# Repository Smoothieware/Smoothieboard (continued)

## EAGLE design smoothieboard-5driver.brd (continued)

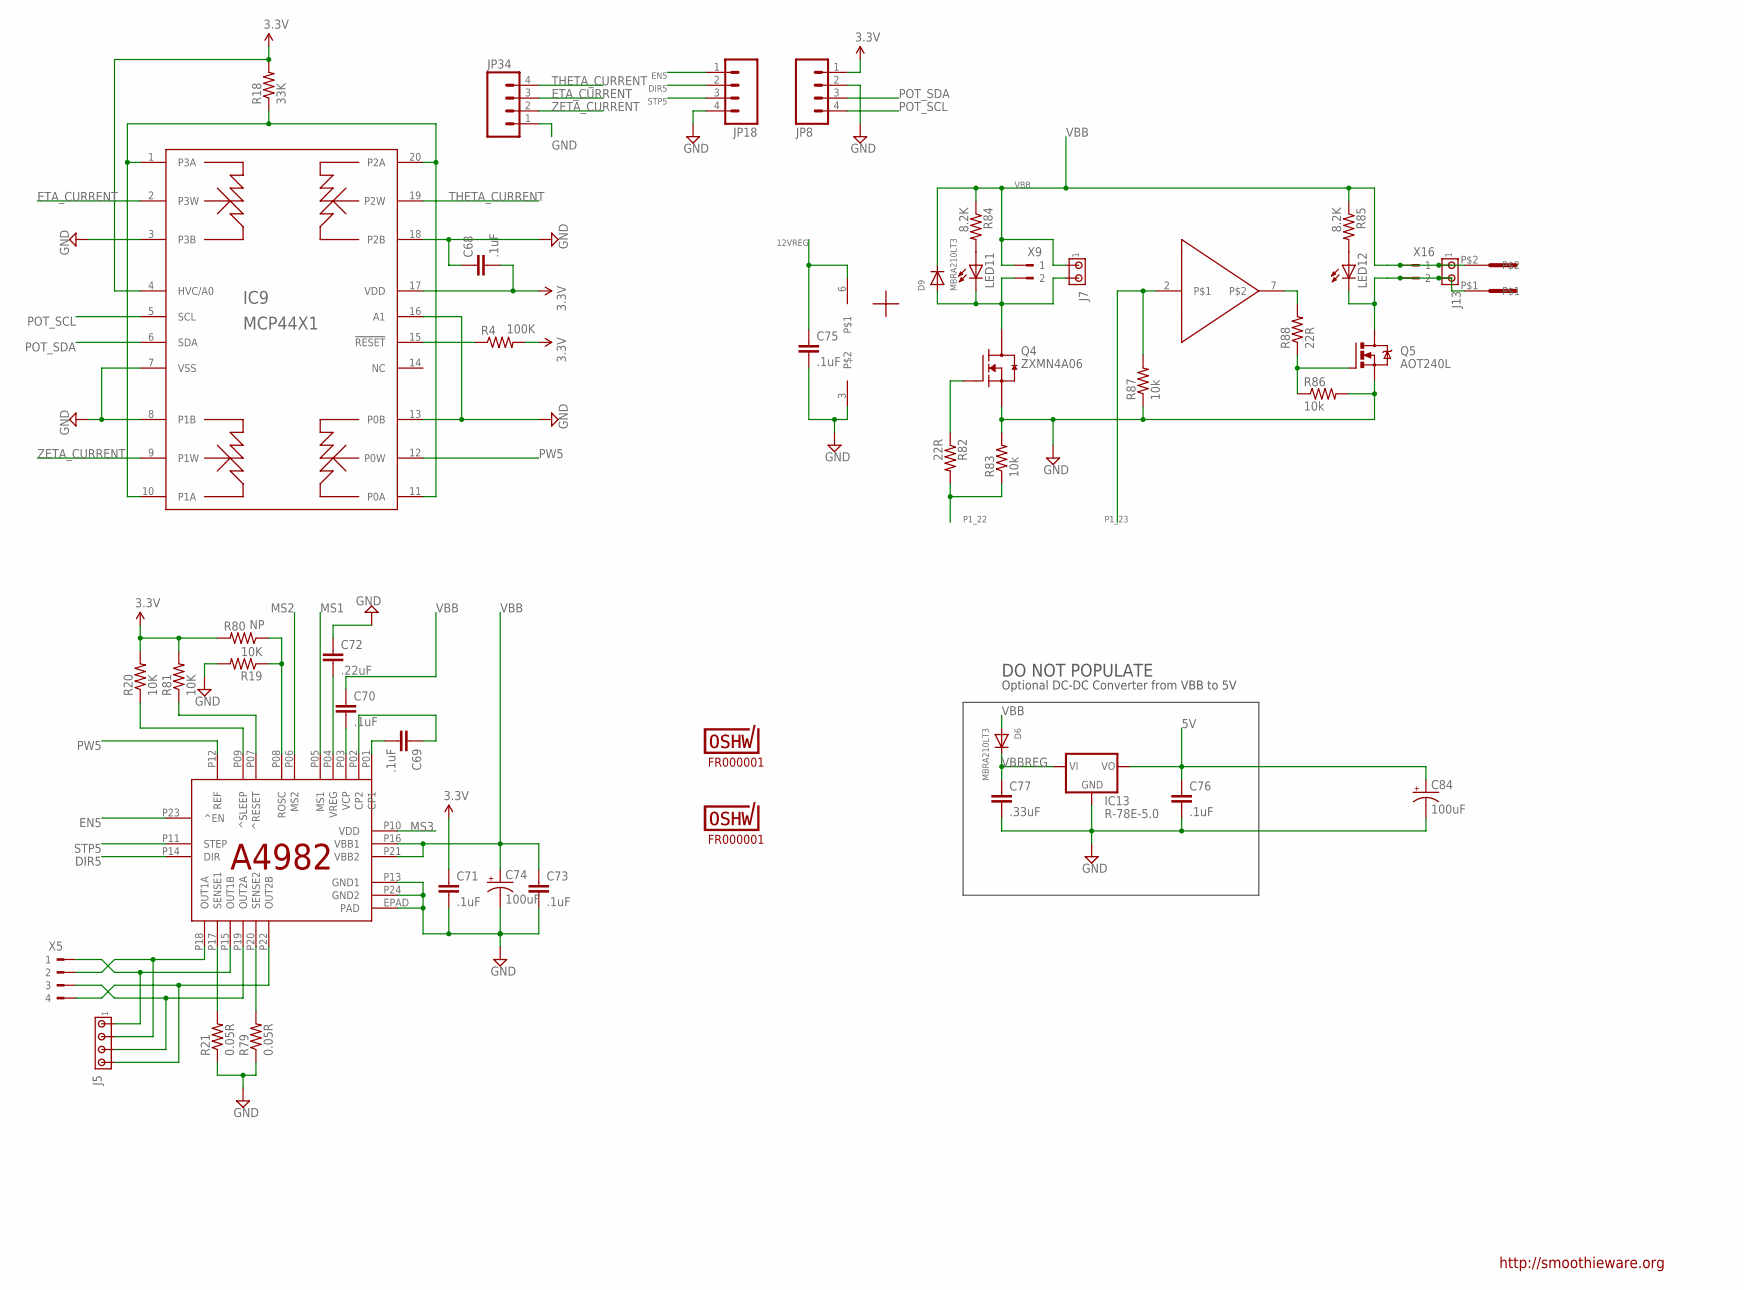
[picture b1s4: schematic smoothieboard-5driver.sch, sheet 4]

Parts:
C68, C69, C70, C71, C73, C75, C76: .1uF; C0603
C72: .22uF; C0603
C74: 100uF; PANASONIC_E
C77: .33uF; C0603
C84: 100uF; PANASONIC_D
D6, D9: MBRA210LT3; SMADIODE
IC9: MCP44X1; TSSOP20
IC12: A5984; ETSSOP24
IC13: R-78E-5.0; R-78
IC15: TC4427; SOIC8
J5: MTA04-100; 10X04MTA
J7, J13: MTA02-100; 10X02MTA
JP8, JP18, JP34: M041X04_NO_SILK; 1X04_NO_SILK
LED11, LED12: LEDCHIP-LED0805; CHIP-LED0805
Q4: ZXMN4A06; SOT230P700X160-4N
Q5: AOT240L; TO220BV
R4: 100K; R0603
R18: 33K; R0603
R19, R20, R81: 10K; R0603
R21, R79: 0.05R; R2512
R80: NP; R0603
R82, R88: 22R; R0603
R83, R86, R87: 10k; R0603
R84, R85: 8.2K; R0603
U$7: 5MMCONN; 1715250000
U$11: FR000001; CERT-SMALL-SILK
U$12: FR000001; CERT-MED-SILK
X5: 180G-4
X9, X16: 180G-2

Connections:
3.3V: C68.2, C71.1, IC9.4 (HVC/A0), IC9.17 (VDD), JP8.1, R4.2, R18.2, R20.2, R80.2, R81.2; also elsewhere on the board
5V: C76.1, C84.+, IC13.3 (VO); also elsewhere on the board
12VREG: C75.1, IC15.6; also elsewhere on the board
DIR5: IC12.P14 (DIR), JP18.2; also elsewhere on the board
EN5: IC12.P23 (^EN), JP18.1; also elsewhere on the board
ETA_CURRENT: IC9.2 (P3W), JP34.3
GND: C68.1, C71.2, C72.1, C73.2, C74.-, C75.2, C76.2, C77.2, C84.-, IC9.3 (P3B), IC9.7 (VSS), IC9.8 (P1B), IC9.13 (P0B), IC9.16 (A1), IC9.18 (P2B), IC12.EPAD (PAD), IC12.P13 (GND1), IC12.P24 (GND2), IC13.2 (GND), IC15.3, JP8.2, JP18.4, JP34.1, Q4.3 (S), Q5.S, R19.2, R21.1, R79.1, R83.2, R86.2, R87.1; also elsewhere on the board
GPIO_FET1: Q5.G, R86.1, R88.1
MS1: IC12.P05 (MS1); also elsewhere on the board
MS2: IC12.P06 (MS2); also elsewhere on the board
MS3: IC12.P10 (VDD); also elsewhere on the board
unnamed: IC9.15 (!RESET), R4.1
unnamed: D9.A, J7.2, LED11.C, Q4.4 (D), X9.2
unnamed: IC9.1 (P3A), IC9.10 (P1A), IC9.11 (P0A), IC9.20 (P2A), R18.1
unnamed: C69.2, IC12.P01 (CP1)
unnamed: C69.1, IC12.P02 (CP2)
unnamed: C70.2, IC12.P03 (VCP)
unnamed: IC12.P17 (SENSE1), R21.2
unnamed: IC12.P20 (SENSE2), R79.2
unnamed: IC12.P18 (OUT1A), J5.2, X5.2
unnamed: IC12.P15 (OUT1B), J5.1, X5.1
unnamed: IC12.P19 (OUT2A), J5.3, X5.3
unnamed: IC12.P22 (OUT2B), J5.4, X5.4
unnamed: IC12.P08 (ROSC), R19.1, R80.1
unnamed: C72.2, IC12.P04 (VREG)
unnamed: IC12.P09 (^SLEEP), R20.1
unnamed: IC12.P07 (^RESET), R81.1
unnamed: Q4.1 (G), R82.1
unnamed: LED11.A, R84.2
unnamed: J13.2, LED12.C, Q5.D, U$7.P$1, X16.2
unnamed: LED12.A, R85.2
unnamed: IC15.7, R88.2
P1_22: R82.2, R83.1; also elsewhere on the board
P1_23: IC15.2, R87.2; also elsewhere on the board
POT_SCL: IC9.5 (SCL), JP8.4; also elsewhere on the board
POT_SDA: IC9.6 (SDA), JP8.3; also elsewhere on the board
PW5: IC9.12 (P0W), IC12.P12 (REF)
STP5: IC12.P11 (STEP), JP18.3; also elsewhere on the board
THETA_CURRENT: IC9.19 (P2W), JP34.4
VBB: C70.1, C73.1, C74.+, D6.A, D9.C, IC12.P16 (VBB1), IC12.P21 (VBB2), J7.1, J13.1, R84.1, R85.1, U$7.P$2, X9.1, X16.1; also elsewhere on the board
VBBREG: C77.1, D6.C, IC13.1 (VI)
ZETA_CURRENT: IC9.9 (P1W), JP34.2

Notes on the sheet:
http://smoothieware.org
DO NOT POPULATE
Optional DC-DC Converter from VBB to 5V

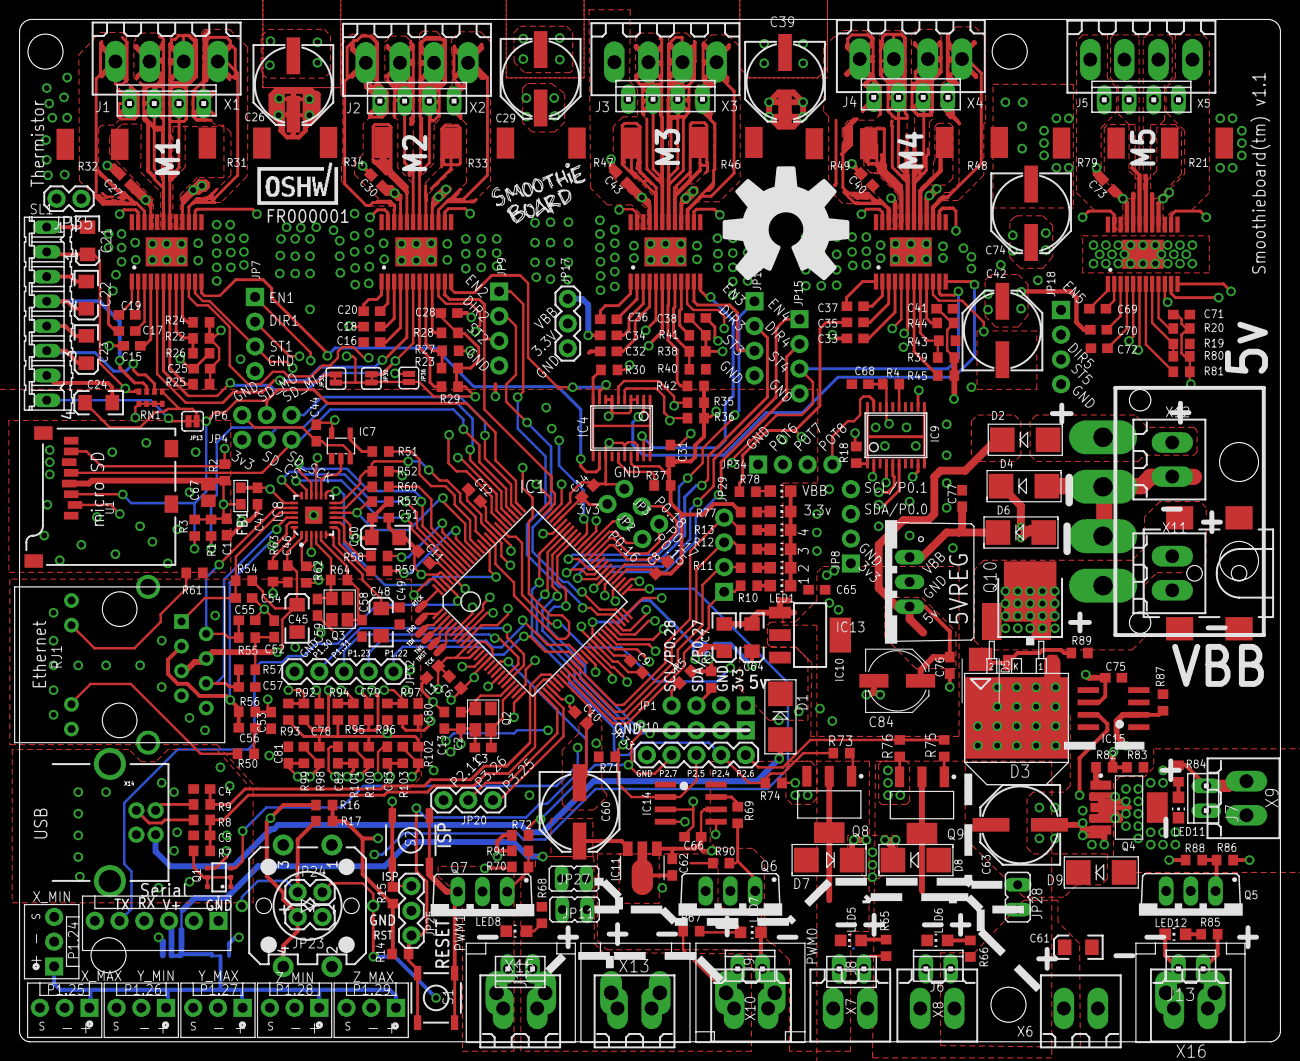
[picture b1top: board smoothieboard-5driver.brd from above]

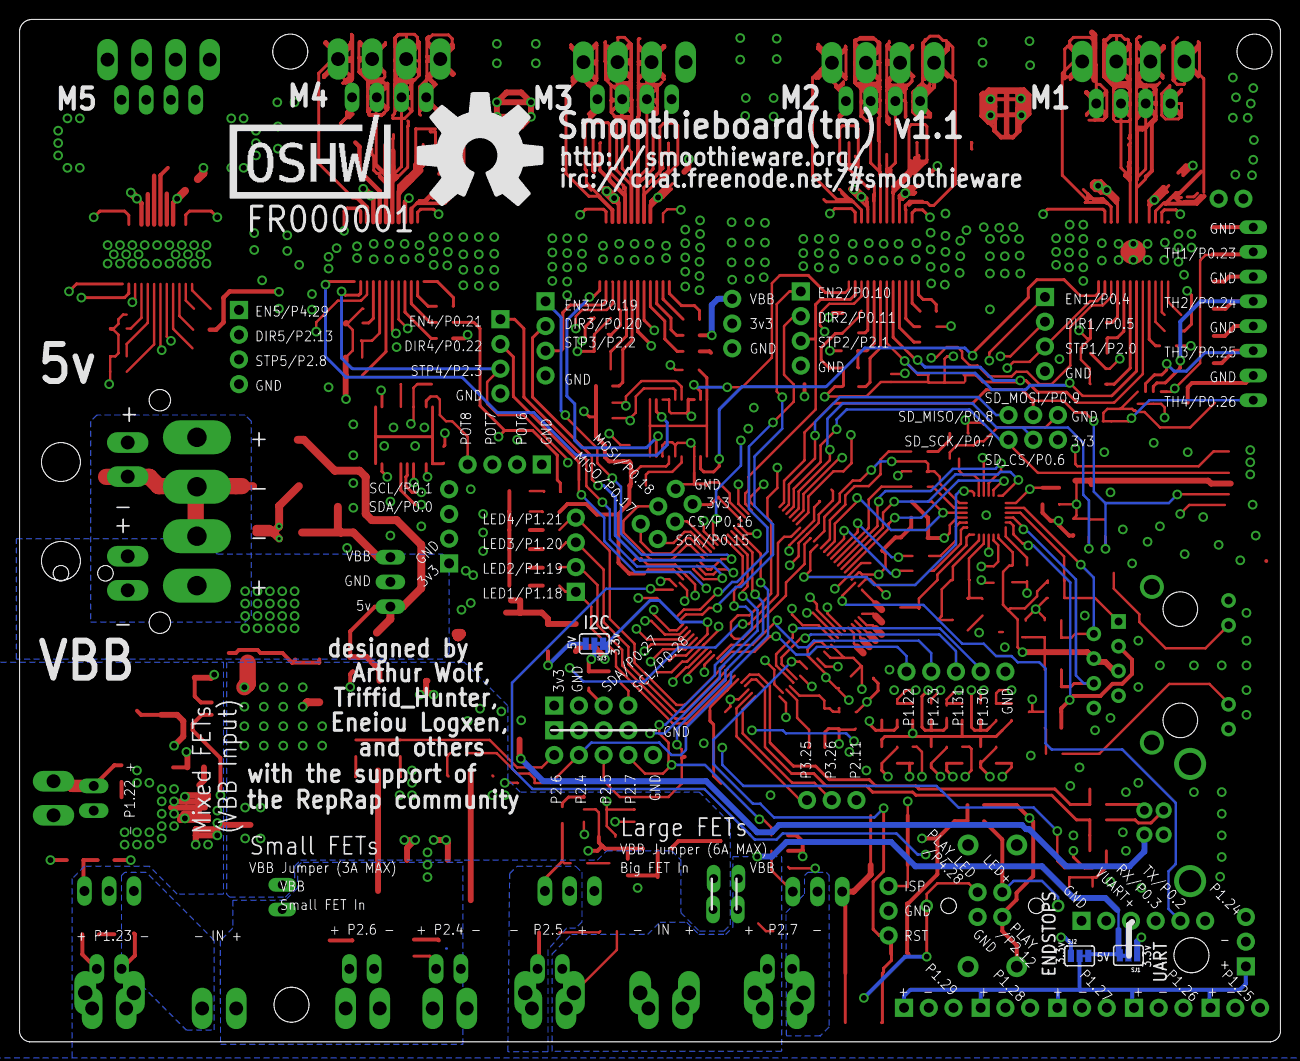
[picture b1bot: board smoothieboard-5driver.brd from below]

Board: 4 copper layers, 129.6 x 105.0 mm, 318 parts (5 on the bottom side), 227 nets.

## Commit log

2012-12-23 initial commit of eagle files
2013-01-09 Added USB-B Connector, other fixes
2013-01-09 Routed SD card ground directly to ground plane
2013-01-09 added BOM
2013-01-09 ignore eagle scratch files
2013-01-09 lots of board cleanup:
    removed thermals on high currenta ares
    HEAPS of trace simplification
    shrink 3v3 plane, use space for other signals
    bulk up many polygons, use ranks to prevent shorts
    separate analog ground, connect thermistors to AVCC/AGND
    make trace angles 45 degrees
2013-01-09 s lcp1768 lpc1769
2013-01-09 vias tented
2013-01-09 give main IC value of LPC1769 to ease BOM generation
2013-01-09 switch 78L12Z for 78L12F surface mount package. also route remaining ratsnest wires- all were traces contacting pad, just not connected to center of pad
2013-01-09 USB-B connector, solder jumper for 5v/3v3 UART power (NOT signals, they're always 3v3)
2013-01-09 switch USB CONNECT transistor for a FET, move UART voltage selector next to UART header
2013-01-09 5v trace was grazing one of the uart pins
2013-01-10 Added polarity mark for TC4427 manually
2013-01-10 Moved C34 to allow heatsink to reach all four drivers from side
2013-01-10 Fixed I2C Header Spacing
2013-01-10 General Silkscreen Cleanup
2013-01-10 Added thermal relief to large caps
2013-01-10 Removed Mosfet Driver Power SMD Jack
2013-01-10 Removed second ground connection from IC11 (to improve MOSFET_DRIVE trace current handling)
2013-01-10 Fixed MOSFET labels on schematic to match BOM
2013-01-10 Changed 78L05 from to-92 to sot-89 in bom, updated USB connector in BOM
2013-01-14 Changed Heated Bed connectors
2013-03-20 Cloned 4driver board to 5driver in preparation for future work. No changes to board yet
2013-03-20 Added 5th driver, 2nd digipot. Still lots of layout work to do
2013-03-23 shifted power connectors, lots of rearranging, still more to do
2013-03-23 added 1x4 connector for 5th driver en/dir/step signals to match other drivers
2013-03-24 Routing complete, DRC passes, now time for fine tuning
2013-03-24 remove VBB poly supplying mosfet drivers from bottom of board to improve driver heatsinking, VBB poly on route15 is adequate.
2013-03-24 Gave small mosfets more heatsink area, moved some signal traces from bottom layer to route15 to improve stepper driver cooling, lots of other tweaks
2013-03-24 Added a bunch of ground stitching vias, also some routing tweaks
2013-03-24 minor routing tweaks
2013-03-24 ditch vestige of STP5 signal's previous incarnation
2013-03-27 Initial placement of extra mosfets
2013-03-31 Extra mosfets routed
2013-03-31 use thermal vias to improve heatsinking for Q4 (small mosfet #3)
2013-03-31 Improve ground plane beneath uC by moving a bunch of traces around
2013-04-01 Change type of primary diode to a more robust type with lower Vf, add a helper diode to prevent damage from primary diode's higher reverse leakage
2013-04-01 Alternative reverse polarity protection using a P-MOSFET. Do not populate both P-MOSFET and Diode footprints, the parts overlap
2013-04-02 add some heatsinking for reverse polarity mosfet on back of board using thermal vias
2013-04-02 Silkscreen text added- M5, VBB, +5v etc part names adjusted Q8 and Q9 aligned 3.5mm footprints added to new mosfets and power input JP32/33 added with ground pins plus necessary rerouting C40 changed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
    probably other misc tweaks and fixes
2013-04-02 move FTDI voltage selection solder jumper to bottom layer
2013-04-02 move name silk for D3 to better position
2013-04-02 added footprint for optional R-78E-5.0 dc-dc converter for converting from VBB to 5V
2013-04-03 add pull-downs on large mosfet gates, tons of silkscreen tidying including labelling of signals in connectors and power routing indicators
2013-04-11 UART voltage selector- add trace to select 5v by default, user must cut trace to select 3.3v
2013-04-11 ensure all connectors include a 3.5mm footprint, remove 0.1" footprint from high current connector, minor routing updates
2013-04-11 add solder pads for JTAG- not enough room to route a proper connector
2013-04-12 reduce I2C pull-up resistors to 2.2k
2013-04-12 Break out digipot I2C bus to a header
2013-04-12 add jumper for VBB power to new mosfets
2013-04-22 Add solder jumper for endstop voltage selection, move labels to _tsilk layer instead of tnames
2013-04-26 Add input protection to endstops
2013-04-29 Smash, move and resize names for endstop protection components
2013-05-01 Move a couple of names off pads, short solder jumpers for x16 microstep by default, ensure A4982's thermal pads have tStop
2013-06-20 added a bit to the readme
2013-06-22 added 0driver board forked from 5driver
2013-07-07 Updated R-78 footprint, i2c V select, orientation marker to ic15, silk updates
2013-09-09 Cleaned up connector placement
2013-10-13 fix endstop input ESD protection
2013-10-14 final fixes for test run of sbc
2013-11-25 remove errant fragments of stop mask, reinstate approved DRC errors
2013-11-26 ensure GND and AGND are connected
2013-12-24 started making the 5driver wiring diagram
2013-12-25 not really sure what changed here but some of the writing somehow ended up the wrong size
2014-05-19 spaced out endstops and corrected sdcard spi header
2014-05-19 updated irc url to chat.freenode.net (irc.freenode.net does not work anymore)
2014-05-19 lots of silk including pinouts on the bottom
2014-06-05 Added CERN license to repo
    The CERN license is the hardware equivalent of the GPL. More info can be
    found at http://www.ohwr.org/projects/cernohl/wiki
2014-06-05 Removed old BoM and 4driver design
2014-06-16 added a touch of extra space between C1 and R1
2016-06-26 Added PDF of schematic for easy access
2016-06-26 Added PDF without filepath caption
2016-06-26 Fixed PDF to include all 4 pages
2016-12-30 Update to v1.1
    Board updated to v1.1. Also added changelog.txt and other some other
    files needed for more complete license compliance.
2017-09-15 added printable template for mounting holes

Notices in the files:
smoothieboard-5driver.sch:
Licensed under GPL: http://www.gnu.org/licenses/gpl.html
parts and their libraries:
SparkFun-Connectors: Licensing: CC v3.0 Share-Alike You are welcome to use this library for commercial purposes.
